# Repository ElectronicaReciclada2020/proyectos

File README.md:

# proyectos
En esta carpeta de Electronica Reciclada publicaremos proyectos open source de dispositivos electronicos o maquinaria industrial

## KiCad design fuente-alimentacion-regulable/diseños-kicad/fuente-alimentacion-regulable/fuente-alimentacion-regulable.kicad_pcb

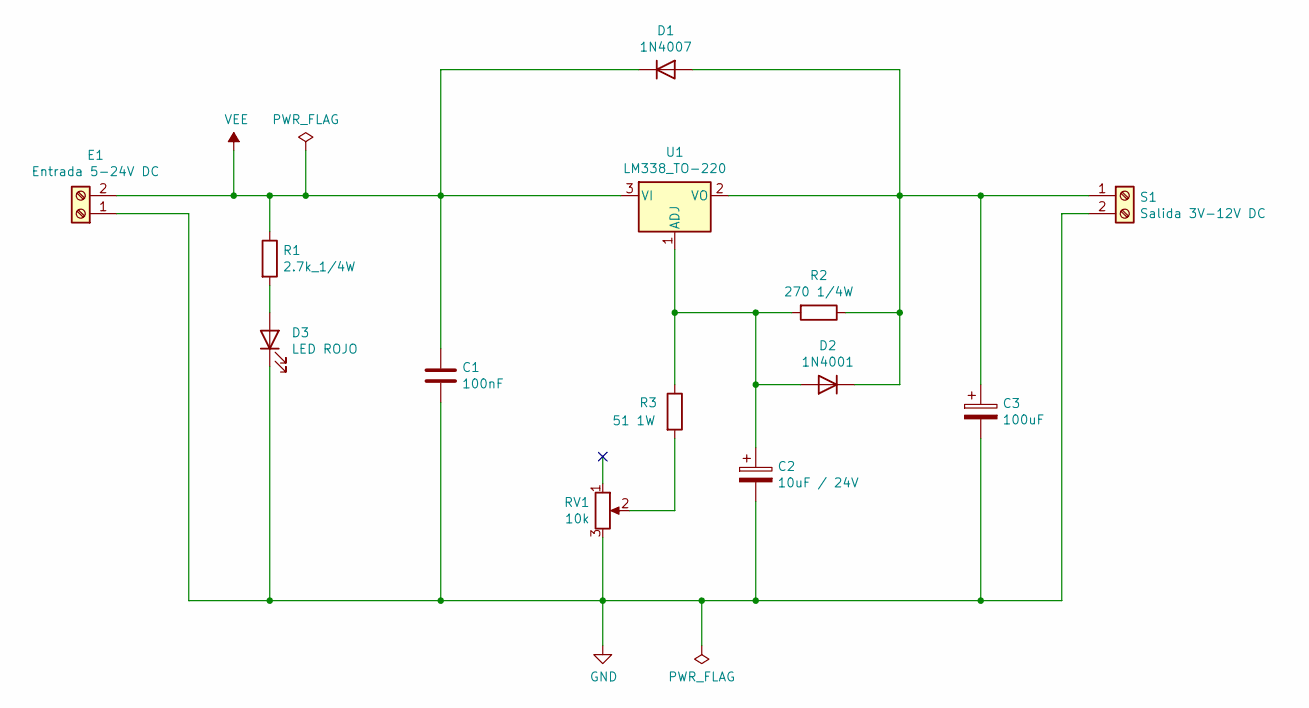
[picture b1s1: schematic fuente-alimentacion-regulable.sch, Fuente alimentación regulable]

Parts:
C1: 100nF; C_Axial_L3.8mm_D2.6mm_P7.50mm_Horizontal
C2: 10uF / 24V; CP_Radial_D5.0mm_P2.50mm
C3: 100uF; CP_Radial_D5.0mm_P2.50mm
D1: 1N4007; D_DO-41_SOD81_P10.16mm_Horizontal
D2: 1N4001; D_DO-41_SOD81_P10.16mm_Horizontal
D3: LED ROJO; LED_D5.0mm
E1: Entrada 5-24V DC; PhoenixContact_MKDS_1,5_2-1727010-1x02_P3.50mm
R1: 2.7k_1/4W; R_Axial_DIN0309_L9.0mm_D3.2mm_P15.24mm_Horizontal
R2: 270 1/4W; R_Axial_DIN0309_L9.0mm_D3.2mm_P15.24mm_Horizontal
R3: 51 1W; R_Axial_DIN0309_L9.0mm_D3.2mm_P15.24mm_Horizontal
RV1: 10k; PhoenixContact_MKDS_1,5_3-19325191-1x03_P3.50mm
S1: Salida 3V-12V DC; PhoenixContact_MKDS_1,5_2-1727010-1x02_P3.50mm
U1: LM338_TO-220; TO-220-3_Vertical-1mm-Pad0.8

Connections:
GND: C1.2, C2.2, C3.2, D3.1 (K), E1.1, RV1.3, S1.2
unnamed: C2.1, D2.2 (A), R2.2, R3.1, U1.1 (ADJ)
unnamed: C3.1, D1.2 (A), D2.1 (K), R2.1, S1.1, U1.2 (VO)
unnamed: D3.2 (A), R1.2
unnamed: R3.2, RV1.2
VEE: C1.1, D1.1 (K), E1.2, R1.1, U1.3 (VI)

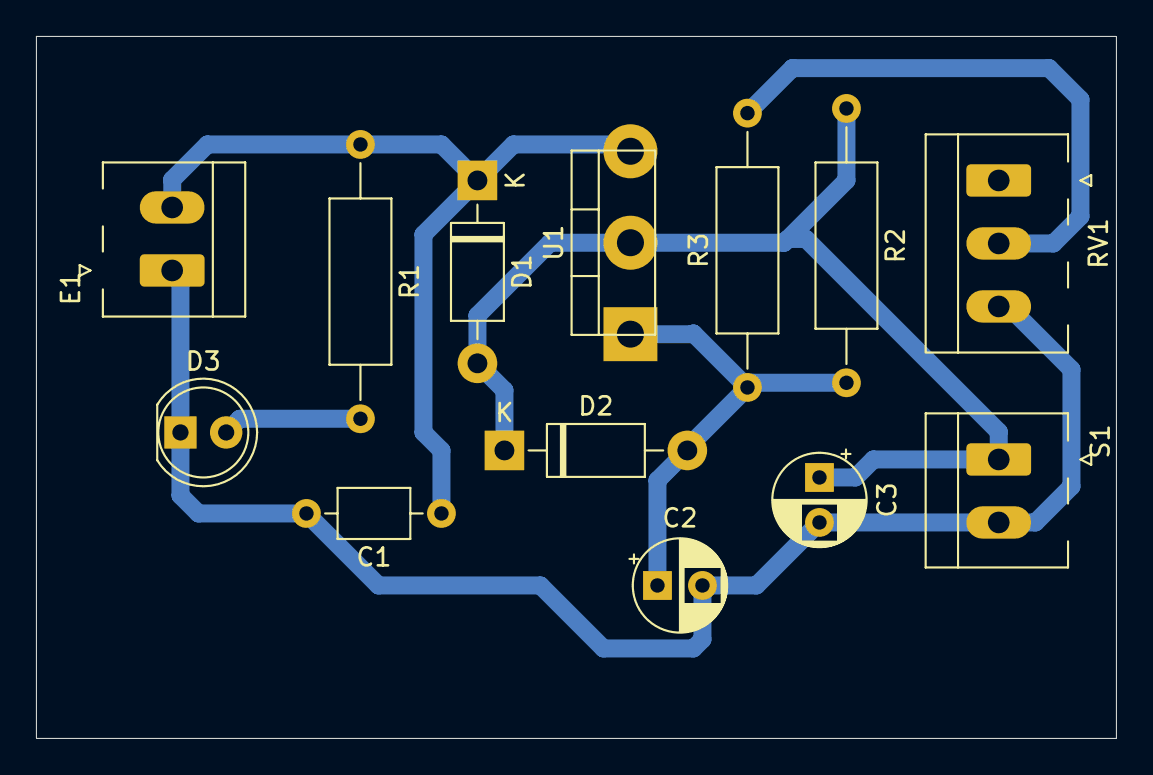
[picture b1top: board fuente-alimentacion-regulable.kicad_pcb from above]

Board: 2 copper layers, 60.0 x 39.0 mm, 13 parts (0 on the bottom side), 6 nets.

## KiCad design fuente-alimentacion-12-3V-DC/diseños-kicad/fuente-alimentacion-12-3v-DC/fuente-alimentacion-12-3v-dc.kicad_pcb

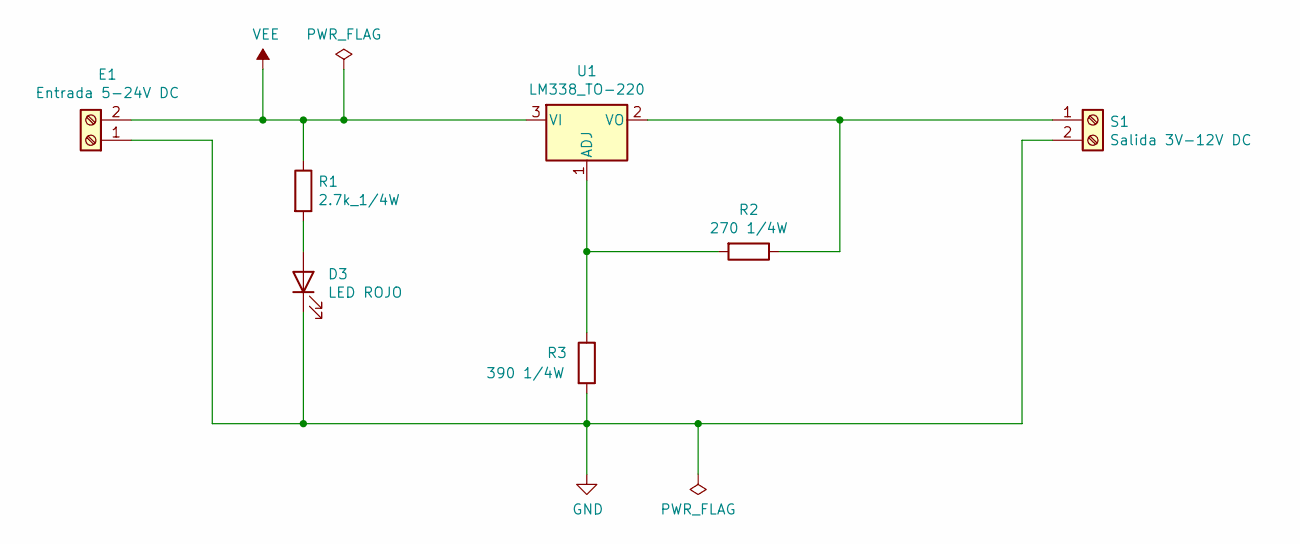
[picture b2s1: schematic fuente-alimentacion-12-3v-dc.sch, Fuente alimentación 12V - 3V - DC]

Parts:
D3: LED ROJO; LED_D5.0mm
E1: Entrada 5-24V DC; PhoenixContact_MKDS_1,5_2-1727010-1x02_P3.50mm
R1: 2.7k_1/4W; R_Axial_DIN0309_L9.0mm_D3.2mm_P15.24mm_Horizontal
R2: 270 1/4W; R_Axial_DIN0309_L9.0mm_D3.2mm_P15.24mm_Horizontal
R3: 390 1/4W; R_Axial_DIN0309_L9.0mm_D3.2mm_P15.24mm_Horizontal
S1: Salida 3V-12V DC; PhoenixContact_MKDS_1,5_2-1727010-1x02_P3.50mm
U1: LM338_TO-220; TO-220-3_Vertical

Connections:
GND: D3.1 (K), E1.1, R3.2, S1.2
unnamed: D3.2 (A), R1.2
unnamed: R2.1, S1.1, U1.2 (VO)
unnamed: R2.2, R3.1, U1.1 (ADJ)
VEE: E1.2, R1.1, U1.3 (VI)

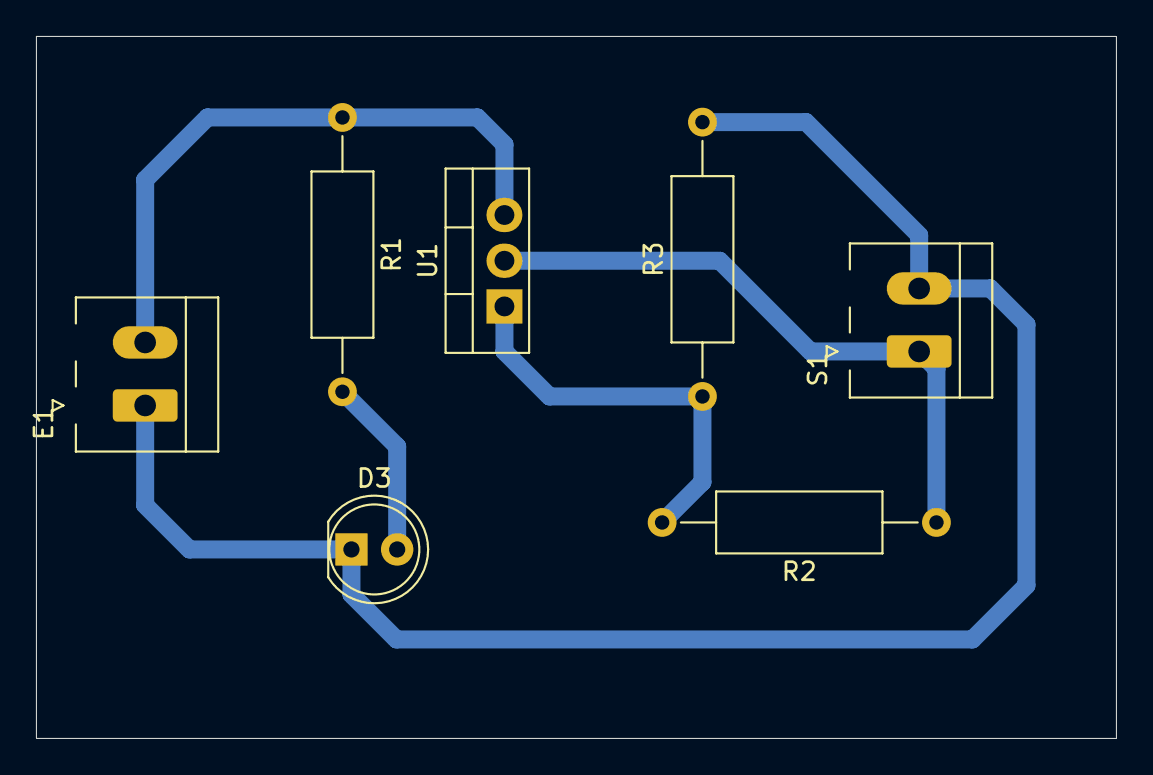
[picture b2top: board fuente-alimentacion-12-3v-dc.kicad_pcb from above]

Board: 2 copper layers, 60.0 x 39.0 mm, 7 parts (0 on the bottom side), 5 nets.

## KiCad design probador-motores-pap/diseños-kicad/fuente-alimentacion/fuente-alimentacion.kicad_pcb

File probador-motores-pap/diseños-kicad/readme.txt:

*En la version V2.0 de la fuente de alimentación se realiza el diseño de la pcb para poder realizarla manualmente en casa con un rotulador, los taladros con una CNC 2018, y el atacado con cloruro férrico.

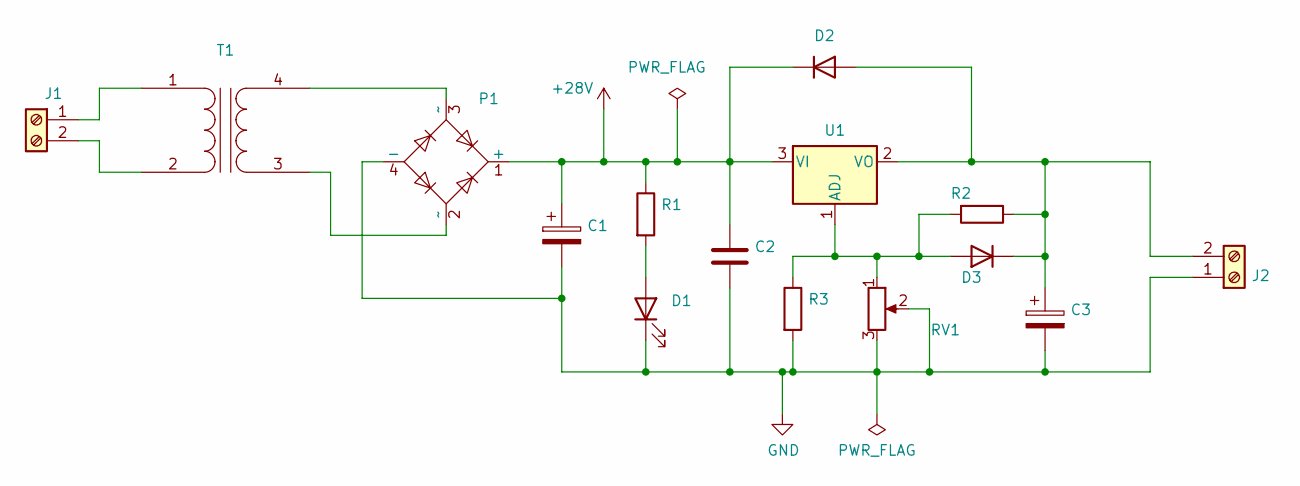
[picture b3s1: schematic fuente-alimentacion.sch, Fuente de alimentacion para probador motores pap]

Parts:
C1: 10000uF_63V; CP_Radial_D8.0mm_P2.50mm
C2: 0.1uF; C_Axial_L5.1mm_D3.1mm_P7.50mm_Horizontal
C3: 2200uF_63V; CP_Radial_D8.0mm_P2.50mm
D1: LED; LED_D8.0mm
D2, D3: 1N4007; D_5W_P5.08mm_Vertical_AnodeUp
J1, J2: Screw_Terminal_01x02; PhoenixContact_MKDS_1,5_2-1727010-1x02_P3.50mm
P1: KBU8J; Diode_Bridge_Vishay_KBU
R1: 2k7_1/4W; R_Axial_DIN0309_L9.0mm_D3.2mm_P15.24mm_Horizontal
R2: 12k_1/4W; R_Axial_DIN0309_L9.0mm_D3.2mm_P12.70mm_Horizontal
R3: 220_1/4W; R_Axial_DIN0309_L9.0mm_D3.2mm_P12.70mm_Horizontal
RV1: 10k; Potentiometer_Bourns_3266Z_Horizontal
T1: VCM 25/1/24; Transformador-VCM_25_1_24
U1: LM338_TO220; TO-220-3_Vertical

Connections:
+28V: C1.1, C2.1, D2.1 (K), P1.1 (+), R1.1, U1.3 (VI)
GND: C1.2, C2.2, C3.2, D1.1 (K), J2.1, P1.4 (-), R3.2, RV1.2, RV1.3
unnamed: C3.1, D2.2 (A), D3.1 (K), J2.2, R2.1, U1.2 (VO)
unnamed: D1.2 (A), R1.2
unnamed: D3.2 (A), R2.2, R3.1, RV1.1, U1.1 (ADJ)
unnamed: J1.1, T1.1 (AA)
unnamed: J1.2, T1.2 (AB)
unnamed: P1.2 (~~), T1.3 (SA)
unnamed: P1.3 (~~), T1.4 (SB)

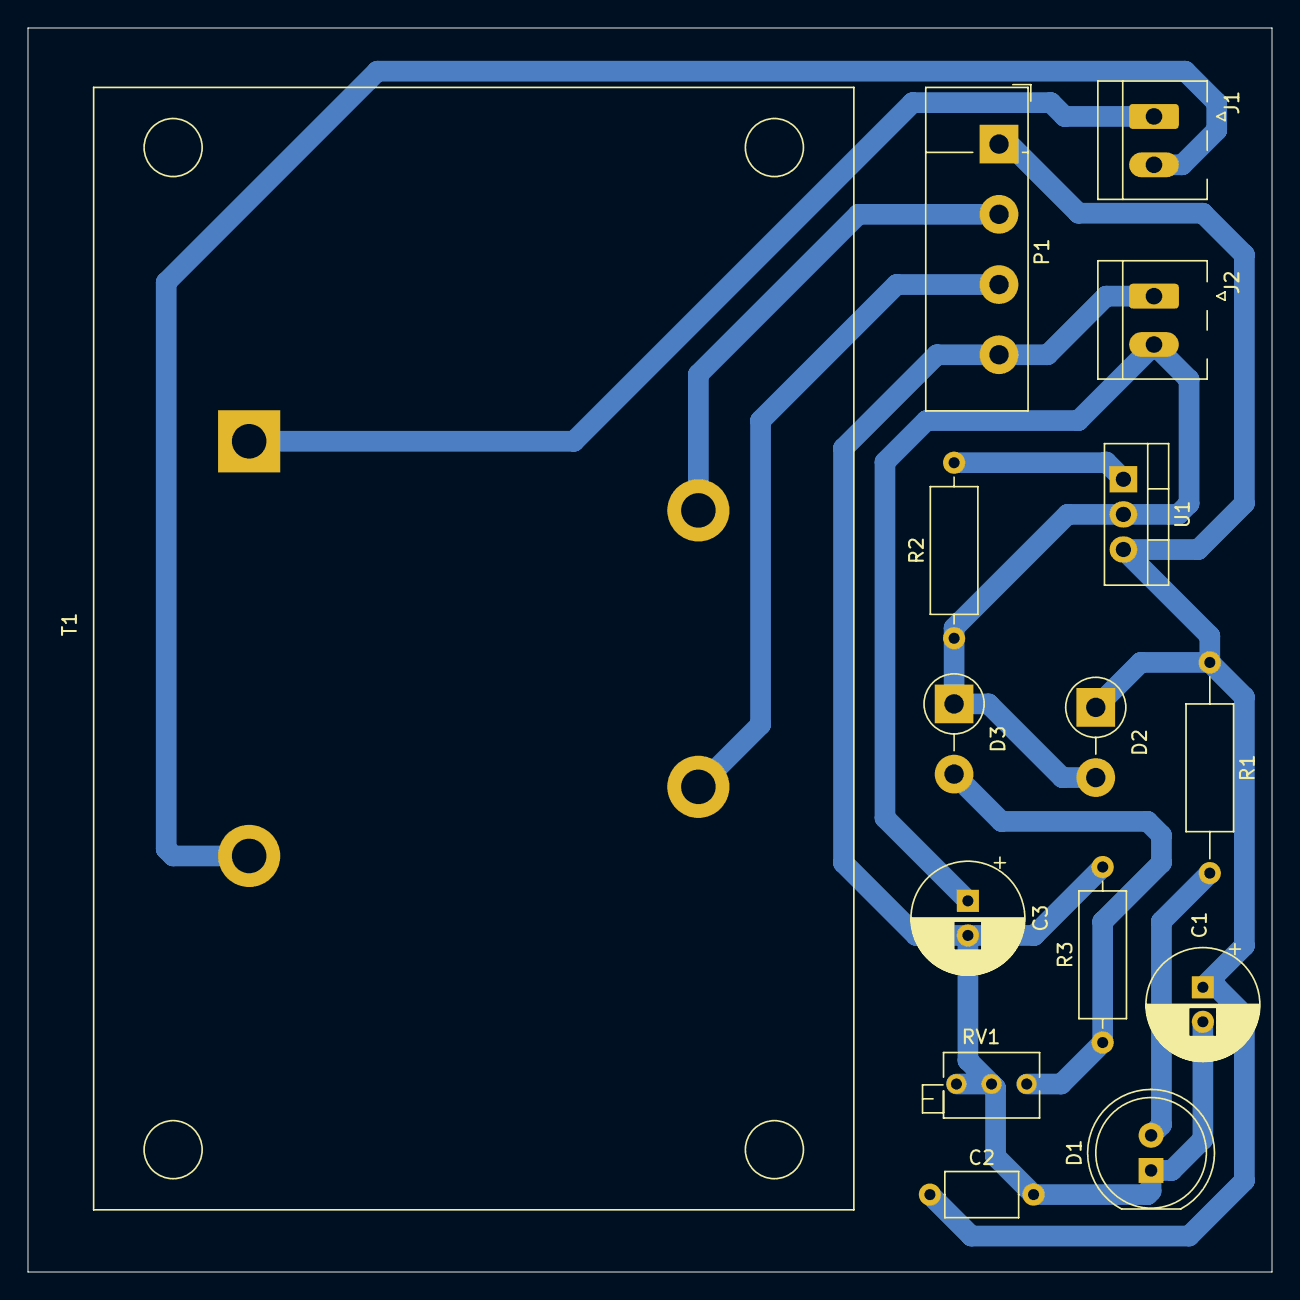
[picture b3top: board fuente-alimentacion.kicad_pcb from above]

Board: 2 copper layers, 90.0 x 90.0 mm, 15 parts (0 on the bottom side), 9 nets.

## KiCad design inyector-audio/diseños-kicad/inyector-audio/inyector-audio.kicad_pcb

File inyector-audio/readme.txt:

Este circuito sirve para poder inyectar una señal de audio en alguno de los equipos electronicos de sonido que necesitamos comprobar su funcionamiento. Tambien nos sirve para poder comprobar altavoces, etc.
En la version 2.0 se rediseña la PCB para poder realizarla de forma casera con rotulador, el taladrado con una CNC y el atacado quimico con cloruro ferrico.
En la version 4.0 se rediseña la PCB se añade un interruptor para que el circuito no se encuentre consumiendo todo el rato de la pila y poder apagarlo cuando no se utiliza.

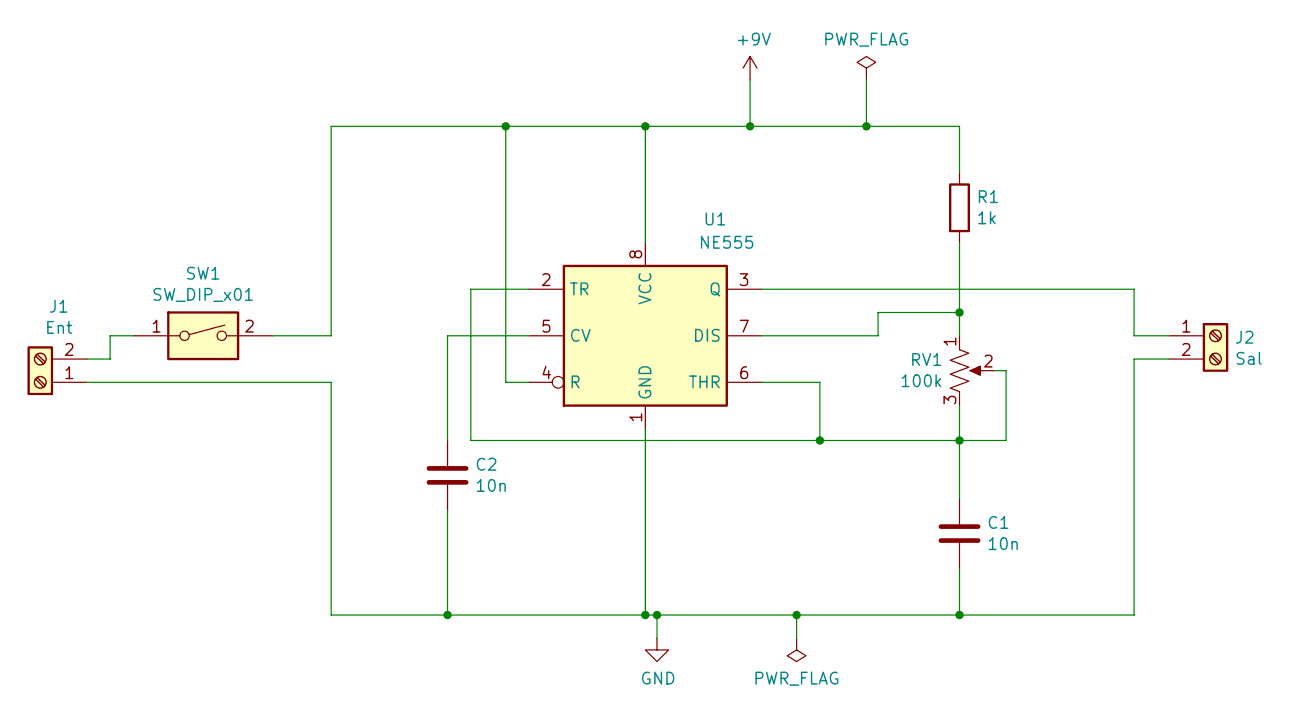
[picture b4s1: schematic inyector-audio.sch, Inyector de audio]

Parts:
C1, C2: 10n; C_Axial_L3.8mm_D2.6mm_P7.50mm_Horizontal
J1: Ent; PinHeader_1x02_P2.00mm_Vertical
J2: Sal; PinHeader_1x02_P2.00mm_Vertical
R1: 1k; R_Axial_DIN0207_L6.3mm_D2.5mm_P10.16mm_Horizontal
RV1: 100k; Potentiometer_ACP_CA6-H2,5_Horizontal
SW1: SW_DIP_x01; PinHeader_1x02_P2.00mm_Vertical
U1: NE555; DIP-8_W7.62mm_Socket

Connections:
+9V: R1.1, SW1.2, U1.4 (R), U1.8 (VCC)
GND: C1.2, C2.2, J1.1, J2.2, U1.1 (GND)
unnamed: C1.1, RV1.2, RV1.3, U1.2 (TR), U1.6 (THR)
unnamed: C2.1, U1.5 (CV)
unnamed: J1.2, SW1.1
unnamed: J2.1, U1.3 (Q)
unnamed: R1.2, RV1.1, U1.7 (DIS)

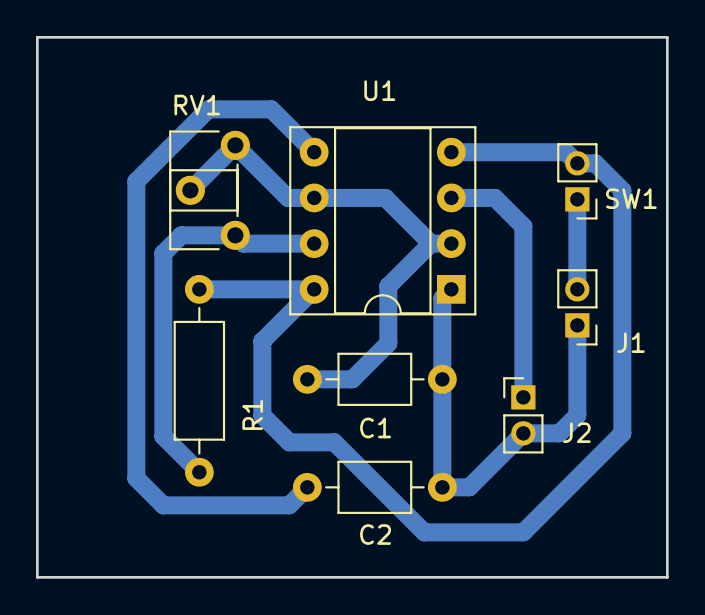
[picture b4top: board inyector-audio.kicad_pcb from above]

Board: 2 copper layers, 35.0 x 30.0 mm, 8 parts (0 on the bottom side), 7 nets.
